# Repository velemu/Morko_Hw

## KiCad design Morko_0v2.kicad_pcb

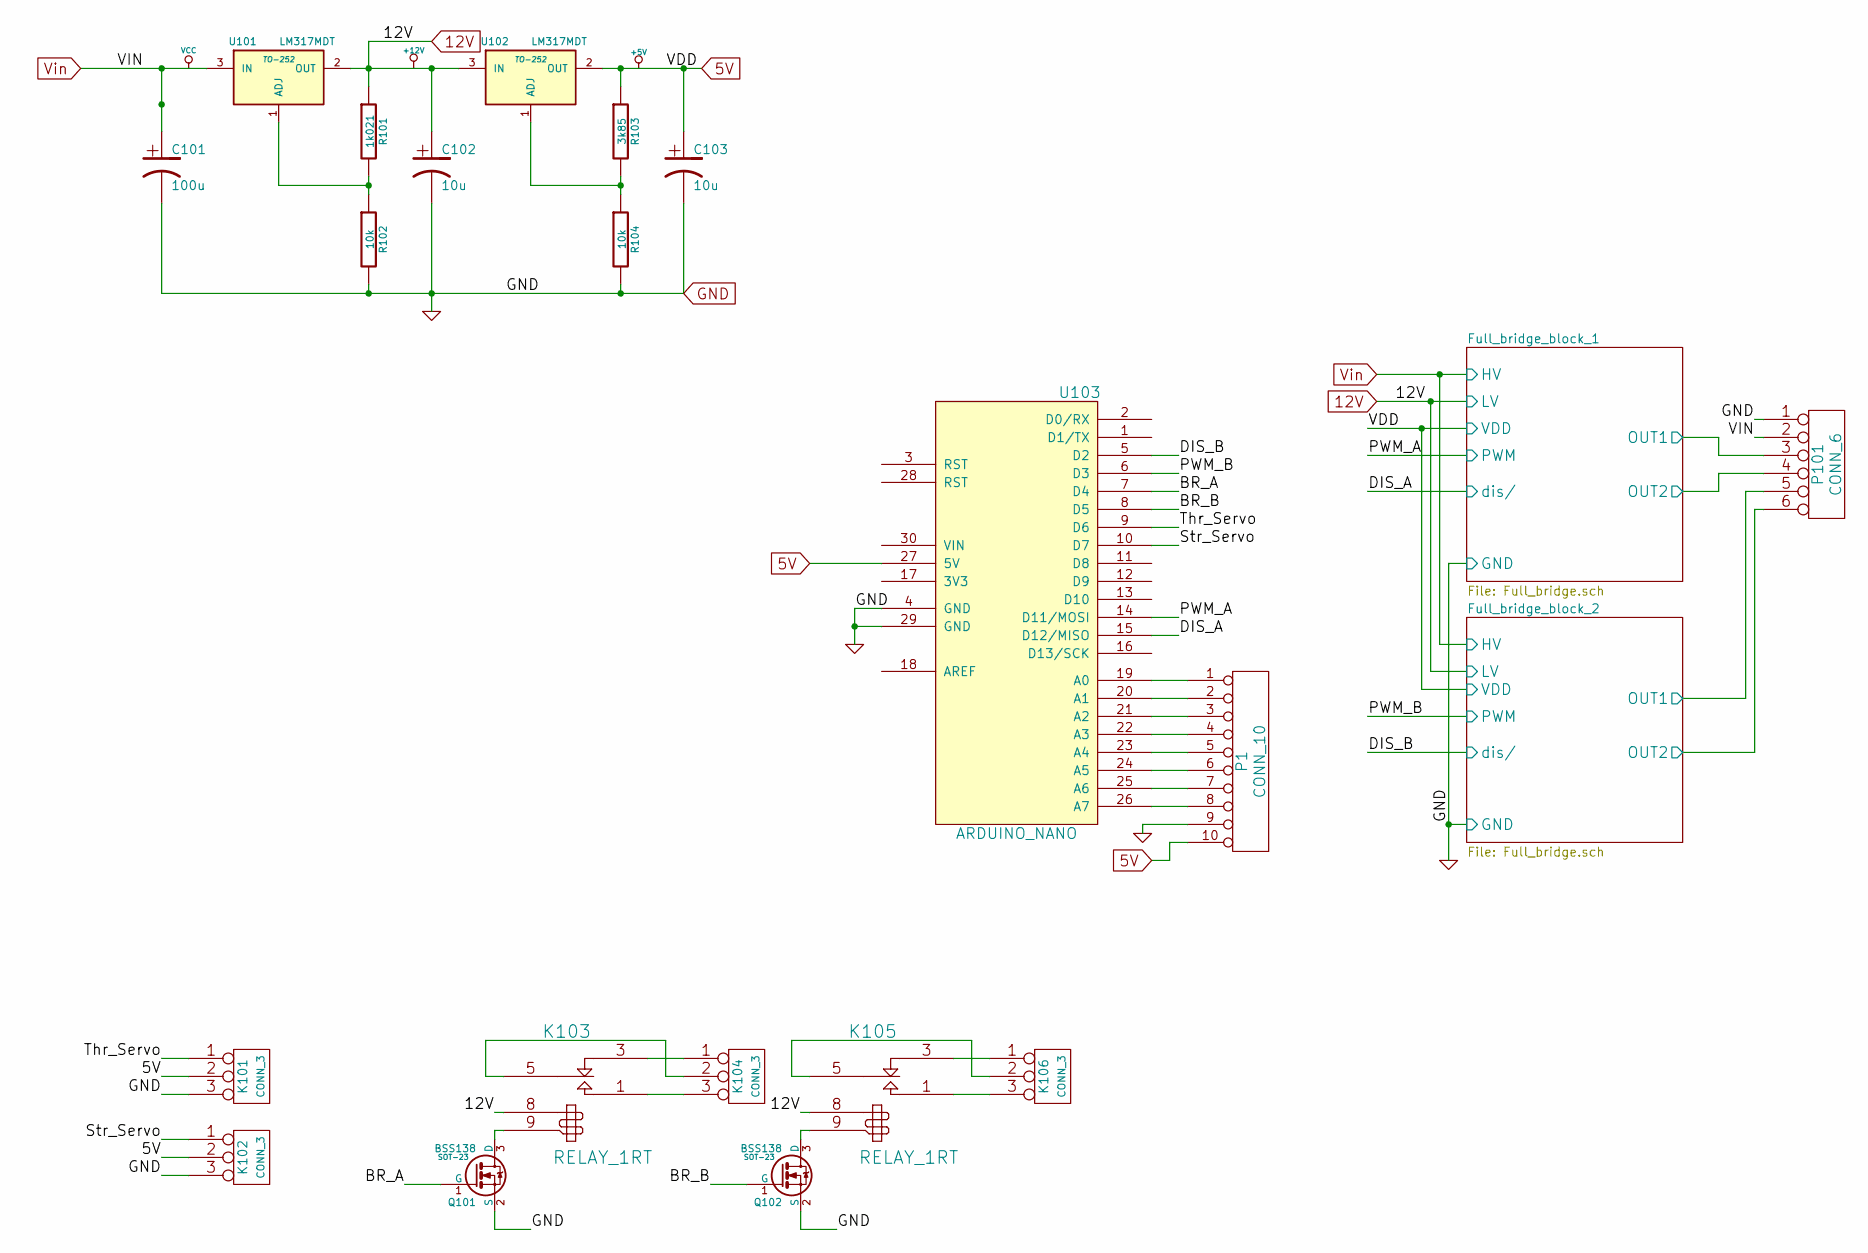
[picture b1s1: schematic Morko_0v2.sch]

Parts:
C101: 100u
C102, C103: 10u
K101, K102, K104, K106: CONN_3
K103, K105: RELAY_1RT
P1: CONN_10
P101: CONN_6
Q101, Q102: BSS138; SOT-23
R101: 1k021
R102, R104: 10k
R103: 3k85
U101, U102: LM317MDT; TO-252
U103: ARDUINO_NANO

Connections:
5V: C103.1, K101.2 (PM), K102.2 (PM), P1.10, R103.1, U102.2 (OUT), U103.27 (5V); also elsewhere on the board
12V: C102.1, K103.8, K105.8, R101.1, U101.2 (OUT), U102.3 (IN); also elsewhere on the board
/BR_A: Q101.1 (G), U103.7 (D4)
/BR_B: Q102.1 (G), U103.8 (D5)
/Full_bridge_block_1/OUT1: P101.3; also elsewhere on the board
/Full_bridge_block_1/OUT2: P101.4; also elsewhere on the board
/Full_bridge_block_1/PWM: U103.14 (D11/MOSI); also elsewhere on the board
/Full_bridge_block_1/dis/: U103.15 (D12/MISO); also elsewhere on the board
/Full_bridge_block_2/OUT1: P101.5; also elsewhere on the board
/Full_bridge_block_2/OUT2: P101.6; also elsewhere on the board
/Full_bridge_block_2/PWM: U103.6 (D3); also elsewhere on the board
/Full_bridge_block_2/dis/: U103.5 (D2); also elsewhere on the board
/Str_Servo: K102.1, U103.10 (D7)
/Thr_Servo: K101.1, U103.9 (D6)
GND: C101.2, C102.2, C103.2, K101.3, K102.3, P1.9, P101.1, Q101.2 (S), Q102.2 (S), R102.2, R104.2, U103.4 (GND), U103.29 (GND); also elsewhere on the board
unnamed: K105.5 (C1), K106.2 (PM)
unnamed: K103.5 (C1), K104.2 (PM)
unnamed: K103.3 (R1), K104.1
unnamed: K103.1 (T1), K104.3
unnamed: K105.1 (T1), K106.3
unnamed: K105.3 (R1), K106.1
unnamed: P1.7, U103.25 (A6)
unnamed: P1.8, U103.26 (A7)
unnamed: P1.6, U103.24 (A5)
unnamed: K105.9, Q102.3 (D)
unnamed: P1.4, U103.22 (A3)
unnamed: P1.5, U103.23 (A4)
unnamed: P1.3, U103.21 (A2)
unnamed: P1.2, U103.20 (A1)
unnamed: P1.1, U103.19 (A0)
unnamed: K103.9, Q101.3 (D)
unnamed: R103.2, R104.1, U102.1 (ADJ)
unnamed: R101.2, R102.1, U101.1 (ADJ)
Vin: C101.1, P101.2, U101.3 (IN); also elsewhere on the board

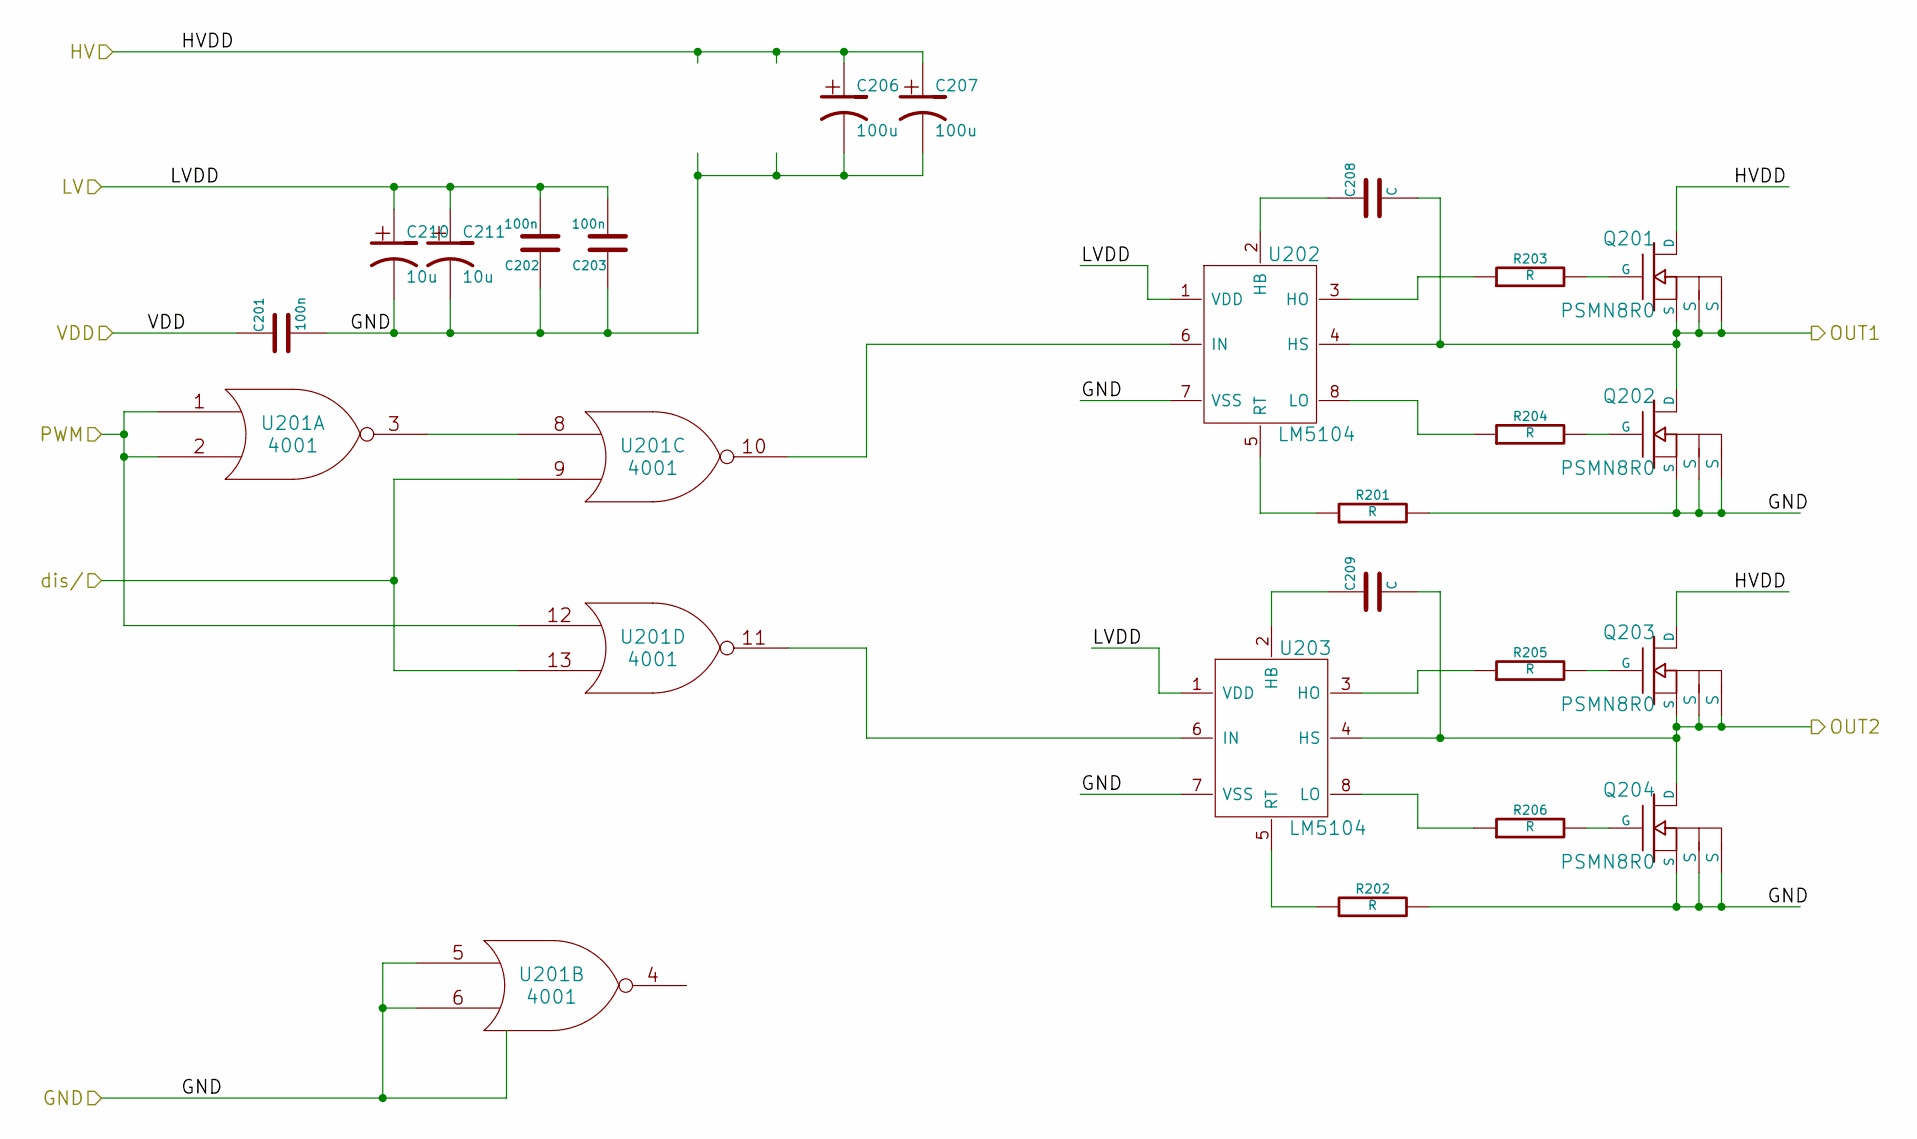
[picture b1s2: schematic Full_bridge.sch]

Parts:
C201, C202, C203: 100n
C206, C207: 100u
C208, C209: C
C210, C211: 10u
Q201, Q202, Q203, Q204: PSMN8R0
R201, R202, R203, R204, R205, R206: R
U201: 4001
U202, U203: LM5104

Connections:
5V: C201.1, U201.14 (VDD); also elsewhere on the board
12V: C202.2, C203.2, C210.1, C211.1, U202.1 (VDD), U203.1 (VDD); also elsewhere on the board
/Full_bridge_block_1/OUT1: C208.2, Q201.1 (S), Q201.2 (S), Q201.3 (S), Q202.5 (D), U202.4 (HS); also elsewhere on the board
/Full_bridge_block_1/OUT2: C209.2, Q203.1 (S), Q203.2 (S), Q203.3 (S), Q204.5 (D), U203.4 (HS); also elsewhere on the board
/Full_bridge_block_1/PWM: U201.1, U201.2, U201.12; also elsewhere on the board
/Full_bridge_block_1/dis/: U201.9, U201.13; also elsewhere on the board
GND: C201.2, C202.1, C203.1, C206.2, C207.2, C210.2, C211.2, Q202.1 (S), Q202.2 (S), Q202.3 (S), Q204.1 (S), Q204.2 (S), Q204.3 (S), R201.2, R202.2, U201.5, U201.6, U201.7 (VSS), U202.7 (VSS), U203.7 (VSS); also elsewhere on the board
unnamed: C208.1, U202.2 (HB)
unnamed: R203.1, U202.3 (HO)
unnamed: R204.1, U202.8 (LO)
unnamed: R205.1, U203.3 (HO)
unnamed: C209.1, U203.2 (HB)
unnamed: U201.10, U202.6 (IN)
unnamed: U201.11, U203.6 (IN)
unnamed: Q201.4 (G), R203.2
unnamed: Q202.4 (G), R204.2
unnamed: Q203.4 (G), R205.2
unnamed: R206.1, U203.8 (LO)
unnamed: Q204.4 (G), R206.2
unnamed: R202.1, U203.5 (RT)
unnamed: R201.1, U202.5 (RT)
unnamed: U201.3, U201.8
Vin: C206.1, C207.1, Q201.5 (D), Q203.5 (D); also elsewhere on the board

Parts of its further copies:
C301, C302, C303: 100n
C306, C307: 100u
C308, C309: C
C310, C311: 10u
Q301, Q302, Q303, Q304: PSMN8R0
R301, R302, R303, R304, R305, R306: R
U301: 4001
U302, U303: LM5104

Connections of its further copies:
5V: C301.1, U301.14 (VDD); also elsewhere on the board
12V: C302.2, C303.2, C310.1, C311.1, U302.1 (VDD), U303.1 (VDD); also elsewhere on the board
/Full_bridge_block_2/OUT1: C308.2, Q301.1 (S), Q301.2 (S), Q301.3 (S), Q302.5 (D), U302.4 (HS); also elsewhere on the board
/Full_bridge_block_2/OUT2: C309.2, Q303.1 (S), Q303.2 (S), Q303.3 (S), Q304.5 (D), U303.4 (HS); also elsewhere on the board
/Full_bridge_block_2/PWM: U301.1, U301.2, U301.12; also elsewhere on the board
/Full_bridge_block_2/dis/: U301.9, U301.13; also elsewhere on the board
GND: C301.2, C302.1, C303.1, C306.2, C307.2, C310.2, C311.2, Q302.1 (S), Q302.2 (S), Q302.3 (S), Q304.1 (S), Q304.2 (S), Q304.3 (S), R301.2, R302.2, U301.5, U301.6, U301.7 (VSS), U302.7 (VSS), U303.7 (VSS); also elsewhere on the board
unnamed: R303.1, U302.3 (HO)
unnamed: C308.1, U302.2 (HB)
unnamed: R304.1, U302.8 (LO)
unnamed: R305.1, U303.3 (HO)
unnamed: C309.1, U303.2 (HB)
unnamed: U301.10, U302.6 (IN)
unnamed: U301.11, U303.6 (IN)
unnamed: Q301.4 (G), R303.2
unnamed: Q302.4 (G), R304.2
unnamed: Q303.4 (G), R305.2
unnamed: R306.1, U303.8 (LO)
unnamed: Q304.4 (G), R306.2
unnamed: R302.1, U303.5 (RT)
unnamed: R301.1, U302.5 (RT)
unnamed: U301.3, U301.8
Vin: C306.1, C307.1, Q301.5 (D), Q303.5 (D); also elsewhere on the board

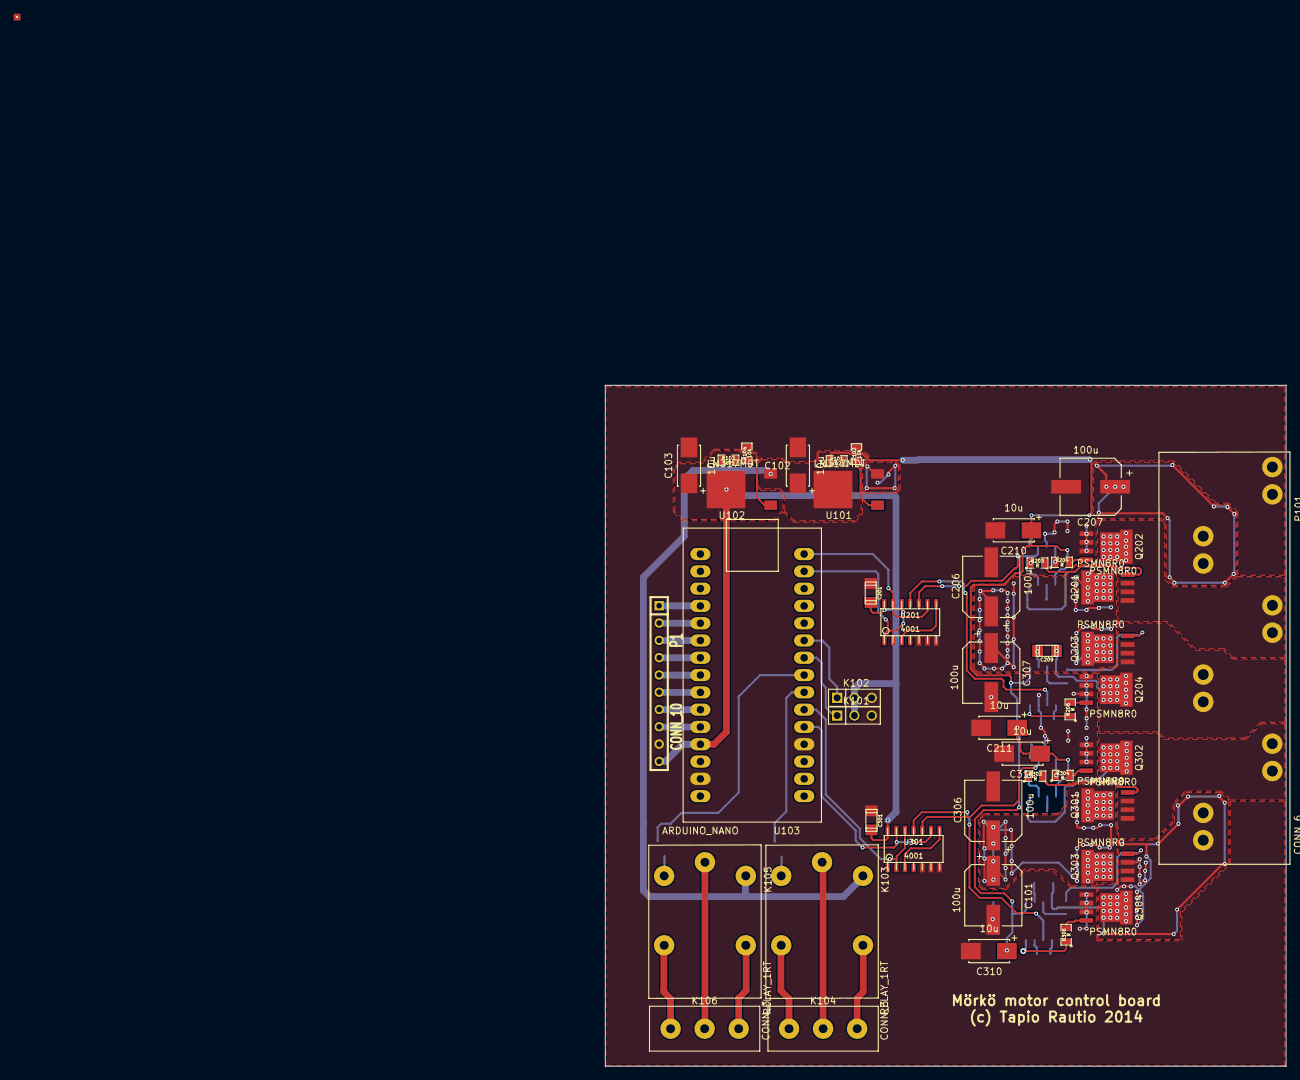
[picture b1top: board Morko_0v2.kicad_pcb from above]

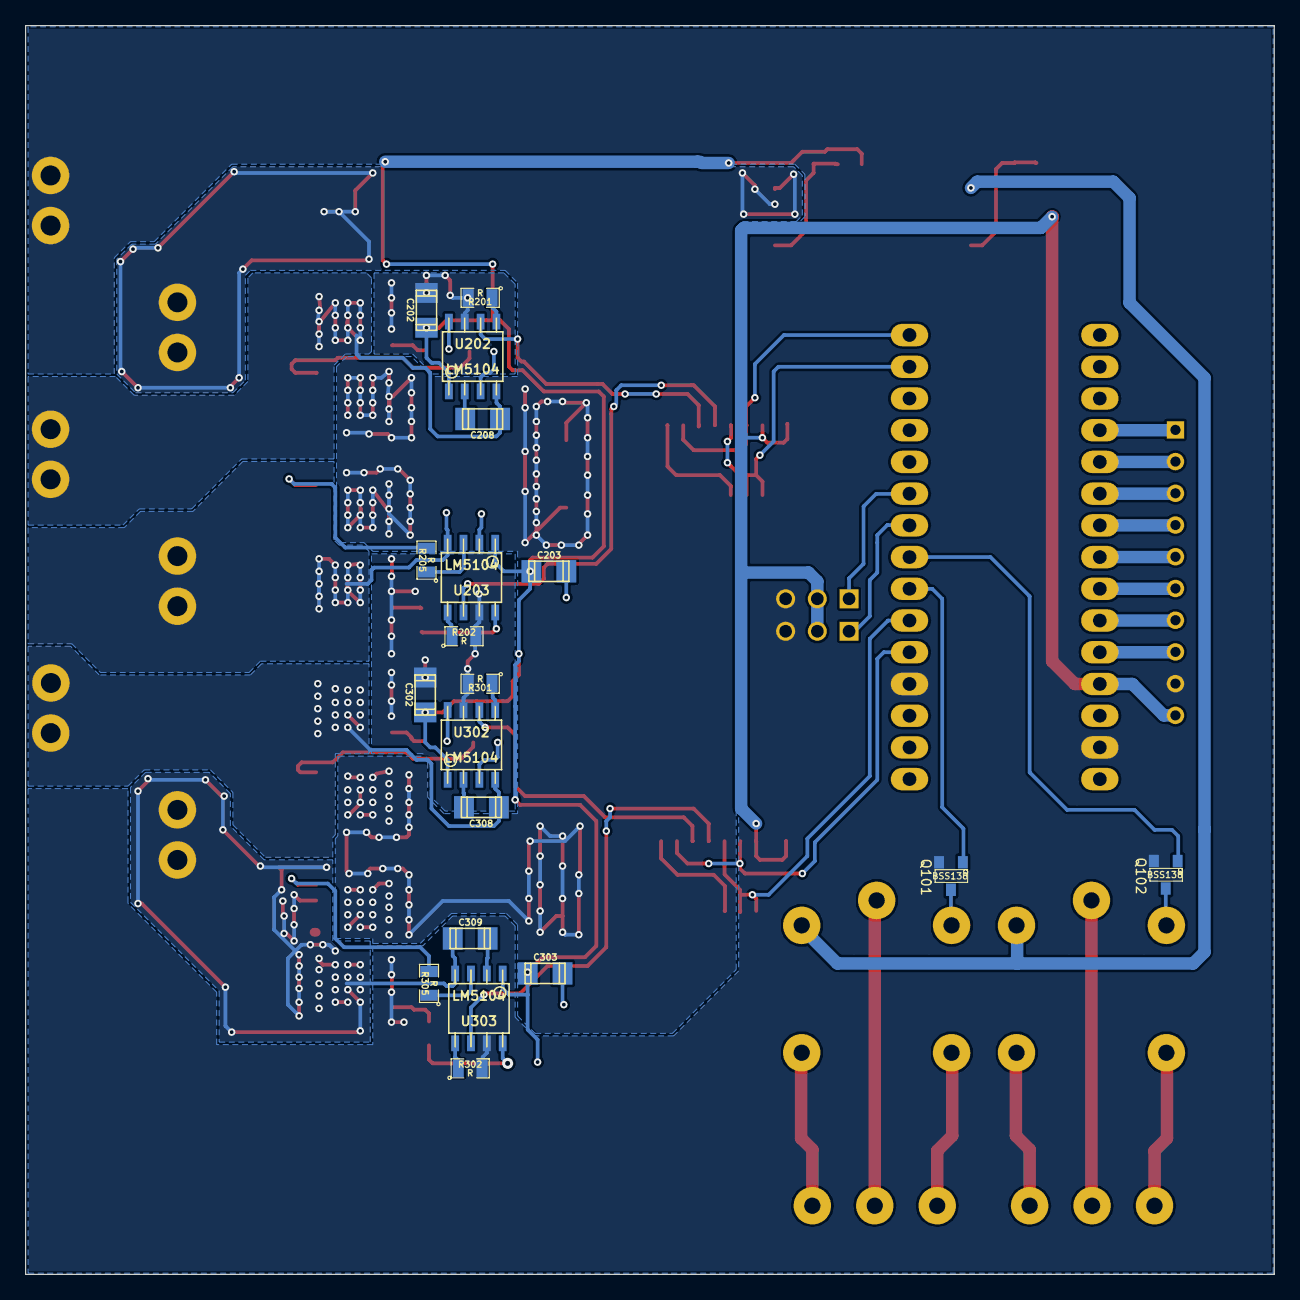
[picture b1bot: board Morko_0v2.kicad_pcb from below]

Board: 2 copper layers, 100.0 x 100.0 mm, 65 parts (19 on the bottom side), 64 nets.

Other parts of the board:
ASTUB: VAL**; ASTUB

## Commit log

2014-11-05 :confetti_ball: Added .gitattributes & .gitignore files
2014-11-05 Tilattu levy
    Tähän on hyvä tehä jatkomuutoksia uuteen versioon
